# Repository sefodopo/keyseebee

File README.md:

# KeySeeBee (modified from [TeXitoi/keyseebee](https://github.com/TeXitoi/keyseebee))

KeySeeBee is a split ergo keyboard. It is only 2 PCB (so the name)
with (almost) only SMD components on it. It's no longer only a keyboard,
it now has keys, USB, rotary encoders, and OLEDs.

The old firmware at [Keyberon](https://github.com/TeXitoi/keyberon), a
pure rust firmware, has not been ported yet as I wanted more of the functionality
that QMK provides without having to code some of those advanced features.

QMK firmware for this version is located [here](https://github.com/sefodopo/qmk_firmware/tree/keyseebee).

## Features

 * 44 keys, using Cherry MX or Kailh choc switches, only 1U keycaps.
 * USB-C connector on the 2 sides.
 * TRRS cable for connecting the 2 halves (for power and UART communication between the 2 halves).
 * 2 STM32F072 MCU, with hardware USB DFU bootloader and crystal less USB;
 * Only onboard SMD components (except for the switches, TRRS
   connector, and optional components).
 * 2 SPI OLED 128x32 3.3V (optional not SMD)
 * 2 EC11 Rotary Encoder (optional not SMD)
 * [Plate files](cad/) (optional).

## Inspiration

 * [Plaid](https://github.com/hsgw/plaid) for "show the components"
 * [GergoPlex](https://www.gboards.ca/product/gergoplex) for "just a keyboard" and "only a PCB with SMD components"
 * [Lily58](https://github.com/kata0510/Lily58) for the thumb cluster
 * [Kyria](https://blog.splitkb.com/blog/introducing-the-kyria) for
   "don't be affraid of pinky stagger"
 * [keyseebee](https://github.com/TeXitoi/keyberon) for initial design without the OLEDs and Encoders and way too many diodes :)

## Gallery

### v0.1, build by TeXitoi

### v0.1, build by TeXitoi, Gateron silent clear (MX footprint), 3D printed plate

### v0.2, build by eropleco, with 1.2mm anodized aluminium plate

### v0.3, build by TeXitoi, Gateron silent clear, 3D printed fat plate

### v0.4, build by Sefodopo, Coming Sometime?

## Bill Of Materials

Price is for 5 keyboards including shipping.

|Item                                                                      |Package|Qty|Remarks                                |Price |
|--------------------------------------------------------------------------|-------|--:|---------------------------------------|-----:|
|[Left PCB](pcb/gerbers/)                                                  |       |  1|Ordered at [JLCPCB](https://jlcpcb.com)|      |
|[Right PCB](pcb/gerbers/)                                                 |       |  1|Ordered at [JLCPCB](https://jlcpcb.com)|33.14€|
|[USB-C connector](https://www.aliexpress.com/item/33004501788.html)       |16 pins|  2|                                       | 1.44€|
|[PJ320A TRRS connector](https://www.aliexpress.com/item/4000661212458.html)|      |  2|                                       | 1.01€|
|[STM32F072CBT6 MCU](https://www.aliexpress.com/item/1005002841528809.html)|LQFP-48|  2|STM32F072C8T6 would also work          | 9.65€|
|[XC6206P332MR regulator](https://www.aliexpress.com/item/33015891307.html)|SOT-23 |  2|Price is for 50                        | 1.93€|
|[SMD switch](https://www.aliexpress.com/item/4000546059630.html)          | 3×6mm |  4|Price is for 100                       | 1.35€|
|[5.1kΩ resistor](https://www.aliexpress.com/item/32865947306.html)        | 0805  |  6|Price is for 100                       |      |
|[1µF capacitor](https://www.aliexpress.com/item/32964553793.html)         | 0805  |  4|Price is for 100                       |      |
|[100nF capacitor](https://www.aliexpress.com/item/32964553793.html)       | 0805  | 10|Price is for 100                       | 3.46€|
|[Bumpers](https://www.aliexpress.com/item/32289191938.html)               | 5×2mm | 10|Price is for 100                       | 1.75€|
|[Cherry MX compatible](https://www.aliexpress.com/item/32836368723.html) or [Kailh Choc](https://www.aliexpress.com/item/1005005883472162.html) switch|5 pins (PCB mount)|44| | |
|1U keycap compatible with the chosen switches                             |       | 44|                                       |      |
|[TRRS cable](https://www.aliexpress.com/item/1005003677396291.html)       |Jack 3.5mm| 1|4 contacts needed                    |      |
|[USB-C cable](https://www.aliexpress.com/item/1005002811739151.html)      |       |  1|USB-2 is enough                        |      |

About 60€ without switches, keycaps and cables for 5 keyboards
(12€/keyboard).

## Compiling and flashing

Follow the QMK guides using my branch of qmk_firmware (or copy my code, idk)... I might add more specific steps in the future.
## What's the layout

Yeah, I'm still figuring it out. I really prefer ZMK and if I can get ZMK working on this keyboard, I'll start using that instead
and update the layout here for what I like.

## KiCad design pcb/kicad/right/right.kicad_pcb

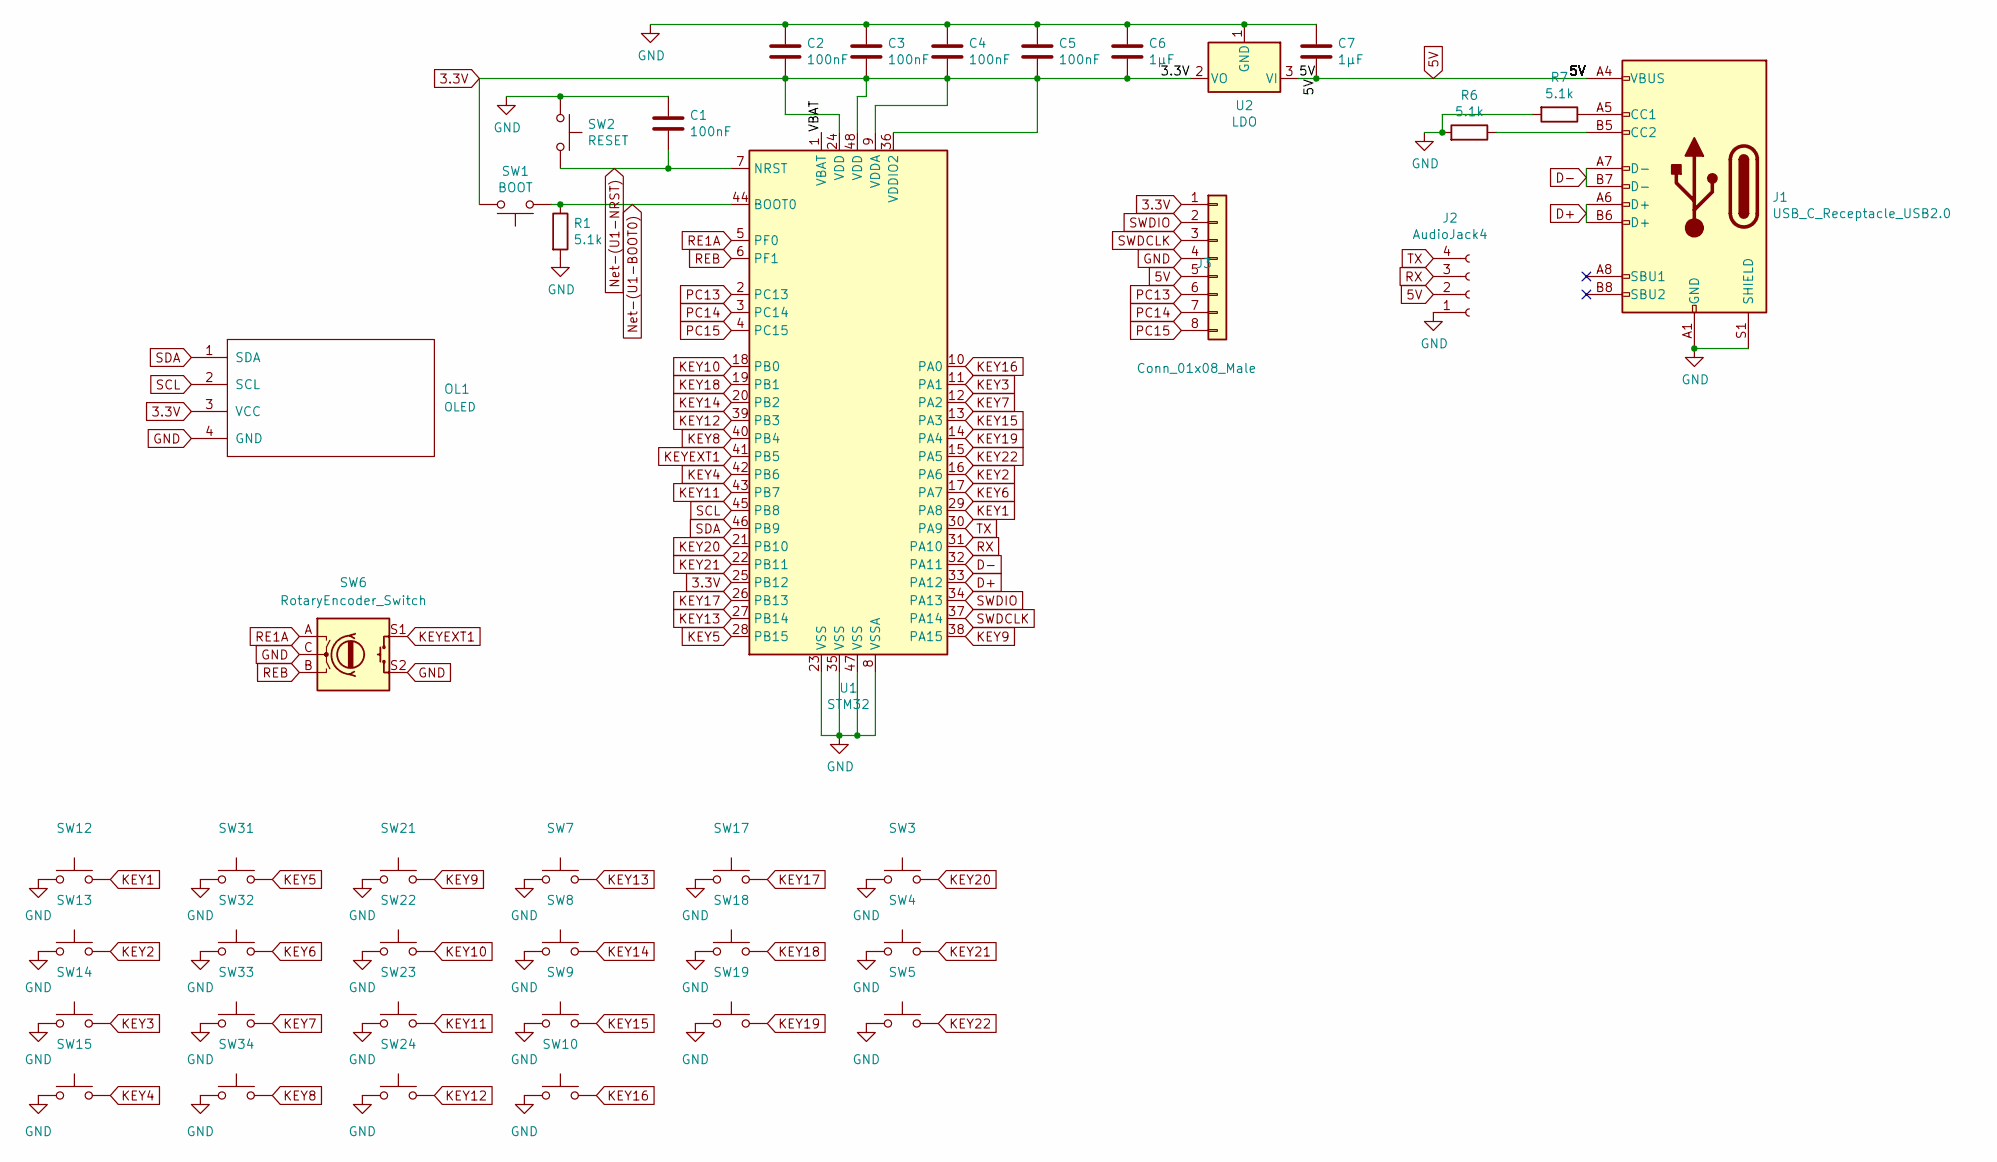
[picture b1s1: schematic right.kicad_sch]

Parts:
C1, C2, C3, C4, C5: 100nF; C_0805_2012Metric_Pad1.15x1.40mm_HandSolder
C6, C7: 1µF; C_0805_2012Metric_Pad1.15x1.40mm_HandSolder
J1: USB_C_Receptacle_USB2.0; USB_C_Receptacle_HRO_TYPE-C-31-M-12
J2: AudioJack4; TRRS-PJ-320A-no-Fmask
J3: Conn_01x08_Male; Harwin_M20-89008xx_1x08_P2.54mm_Horizontal
OL1: OLED; OLED_1side
R1, R6, R7: 5.1k; R_0805_2012Metric_Pad1.15x1.40mm_HandSolder
SW1: BOOT; SW_SPST_CK_RS282G05A3
SW2: RESET; SW_SPST_CK_RS282G05A3
SW3, SW4, SW5, SW7, SW8, SW9, SW10, SW12, SW13, SW14, SW15, SW17, SW18, SW19, SW21, SW22, SW23, SW24, SW31, SW32, SW33, SW34: SW_Push; CherryMX_Choc_MXHotswap_1u
SW6: RotaryEncoder_Switch; RotaryEncoder_Alps_EC11E-Switch_Vertical_H20mm
U1: STM32; LQFP-48_7x7mm_P0.5mm
U2: LDO; SOT-23

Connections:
3.3V: C2.2, C3.2, C4.2, C5.2, C6.2, J3.1, OL1.3 (VCC), SW1.2, U1.9 (VDDA), U1.24 (VDD), U1.25 (PB12), U1.36 (VDDIO2), U1.48 (VDD), U2.2 (VO)
5V: C7.2, J1.A4 (VBUS), J1.A9 (VBUS), J1.B4 (VBUS), J1.B9 (VBUS), J2.2, J3.5, U2.3 (VI)
/VBAT: U1.1 (VBAT)
D+: J1.A6 (D+), J1.B6 (D+), U1.33 (PA12)
D-: J1.A7 (D-), J1.B7 (D-), U1.32 (PA11)
GND: C1.1, C2.1, C3.1, C4.1, C5.1, C6.1, C7.1, J1.A1 (GND), J1.A12 (GND), J1.B1 (GND), J1.B12 (GND), J1.S1 (SHIELD), J2.1, J3.4, OL1.4 (GND), R1.2, R6.2, R7.2, SW2.1, SW3.2, SW4.2, SW5.2, SW6.C, SW6.S2, SW7.2, SW8.2, SW9.2, SW10.2, SW12.2, SW13.2, SW14.2, SW15.2, SW17.2, SW18.2, SW19.2, SW21.2, SW22.2, SW23.2, SW24.2, SW31.2, SW32.2, SW33.2, SW34.2, U1.8 (VSSA), U1.23 (VSS), U1.35 (VSS), U1.47 (VSS), U2.1 (GND)
KEY1: SW12.1, U1.29 (PA8)
KEY2: SW13.1, U1.16 (PA6)
KEY3: SW14.1, U1.11 (PA1)
KEY4: SW15.1, U1.42 (PB6)
KEY5: SW31.1, U1.28 (PB15)
KEY6: SW32.1, U1.17 (PA7)
KEY7: SW33.1, U1.12 (PA2)
KEY8: SW34.1, U1.40 (PB4)
KEY9: SW21.1, U1.38 (PA15)
KEY10: SW22.1, U1.18 (PB0)
KEY11: SW23.1, U1.43 (PB7)
KEY12: SW24.1, U1.39 (PB3)
KEY13: SW7.1, U1.27 (PB14)
KEY14: SW8.1, U1.20 (PB2)
KEY15: SW9.1, U1.13 (PA3)
KEY16: SW10.1, U1.10 (PA0)
KEY17: SW17.1, U1.26 (PB13)
KEY18: SW18.1, U1.19 (PB1)
KEY19: SW19.1, U1.14 (PA4)
KEY20: SW3.1, U1.21 (PB10)
KEY21: SW4.1, U1.22 (PB11)
KEY22: SW5.1, U1.15 (PA5)
KEYEXT1: SW6.S1, U1.41 (PB5)
unnamed: J1.A5 (CC1), R7.1
unnamed: J1.B5 (CC2), R6.1
unnamed: R1.1, SW1.1, U1.44 (BOOT0)
unnamed: C1.2, SW2.2, U1.7 (NRST)
PC13: J3.6, U1.2 (PC13)
PC14: J3.7, U1.3 (PC14)
PC15: J3.8, U1.4 (PC15)
RE1A: SW6.A, U1.5 (PF0)
REB: SW6.B, U1.6 (PF1)
RX: J2.3, U1.31 (PA10)
SCL: OL1.2 (SCL), U1.45 (PB8)
SDA: OL1.1 (SDA), U1.46 (PB9)
SWDCLK: J3.3, U1.37 (PA14)
SWDIO: J3.2, U1.34 (PA13)
TX: J2.4, U1.30 (PA9)

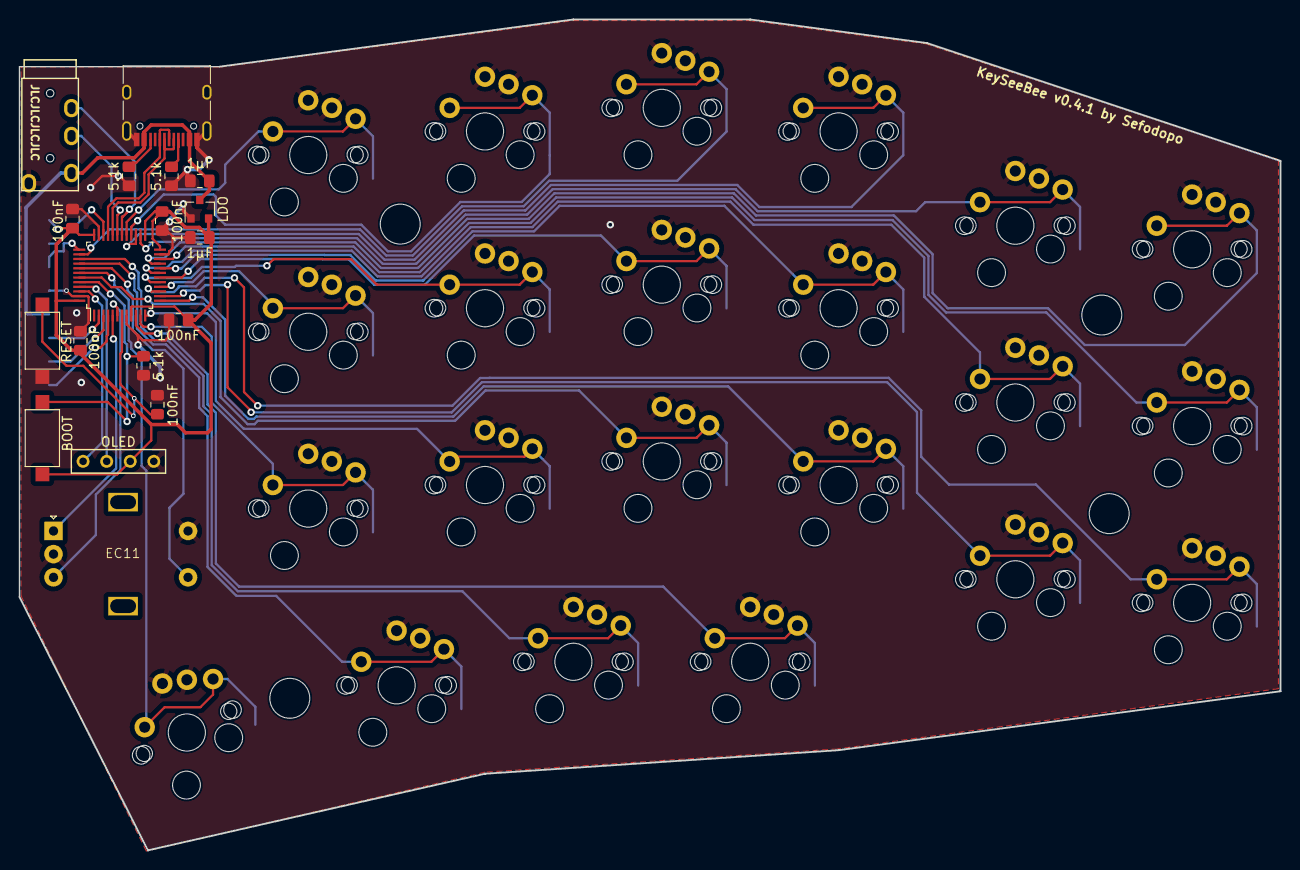
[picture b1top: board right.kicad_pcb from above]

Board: 2 copper layers, 135.9 x 89.5 mm, 41 parts (1 on the bottom side), 43 nets.

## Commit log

2024-04-22 Updated to v0.4.1 with direct wired switches and Rotary Encoders and OLEDS added along with pcb plates
    Be warned that the keyplate is missing a cutout for the rotary encoder
    and OLED module
2024-10-18 Working on top plate
2024-10-18 Working on compromise
2024-10-20 Maybe we don't compromise?
2024-10-21 Think the plate is ready for printing
2024-10-21 Cleaned up a bit, started to make adjustments for future
2024-10-21 Added bottom case
2024-10-21 Fixed formatting
2024-10-21 Fixed tolerances
2024-10-21 Added dovetails
2024-10-21 Added chamfers
2024-10-21 Right side testing with no tent
2024-10-21 Fixed dovetails for right side test
2024-10-21 Right version 1.2 Adjusted tolerances and bottom plate
2024-10-22 Left version 1.3 More adjustments...h
2024-10-22 Fixed overlap causing plate not to insert into top
2024-10-22 Added more dovetails and adjusted screw hole size to work with m2 heat inserts
2024-10-22 Rounded the top edge instead of a chamfer
2024-10-23 Right version 1.4, hopefully last version unless I like the chamfer better than the bevel
2024-10-26 Left version 1.5
2024-10-27 Added tenting
